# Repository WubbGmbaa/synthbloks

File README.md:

## Project to be renamed. Suggestions appreciated.

# SynthBloks
SynthBloks are modular synthesizer modules in a fun form factor.

### Roadmap
Until the first release of this form factor, the standards described here are subject to change, as issues are fixed and features are added. As part of the process involved in designing and testing the form factor, modules will be designed based on pre-existing, open-source circuits. These modules will also serve a secondary purpose as a "proof of concept" to demonstrate the format, and are hosted in the [synthbloks-PoC repository](https://github.com/WubbGmbaa/synthbloks_POC). Once these "proof of concept" modules have been used to test and change the SynthBloks standard form factor, the first release of the form factor (this repository) will be made. After the first official release of the standards described here, modules will be developed from original circuits, and hosted in their own repositories.

### Development
This repository contains documentation about the standard, as well as resources for desiging modules. Technical details about the form factor can be found [within the documentation](../docs/FormFactor.md).
Proof-of-concept modules were previously also held here, but have since been moved to [their own repository](https://github.com/WubbGmbaa/synthbloks_POC).

### Legal Stuff
First-party modules are licensed under a [Creative Commons Attribution-ShareAlike 4.0 International License](http://creativecommons.org/licenses/by-sa/4.0/).
The form factor itself is licensed under a [Creative Commons Attribution-NonCommercial 4.0 International License](http://creativecommons.org/licenses/by-nc/4.0/).
Third-party modules are the property of their creators.

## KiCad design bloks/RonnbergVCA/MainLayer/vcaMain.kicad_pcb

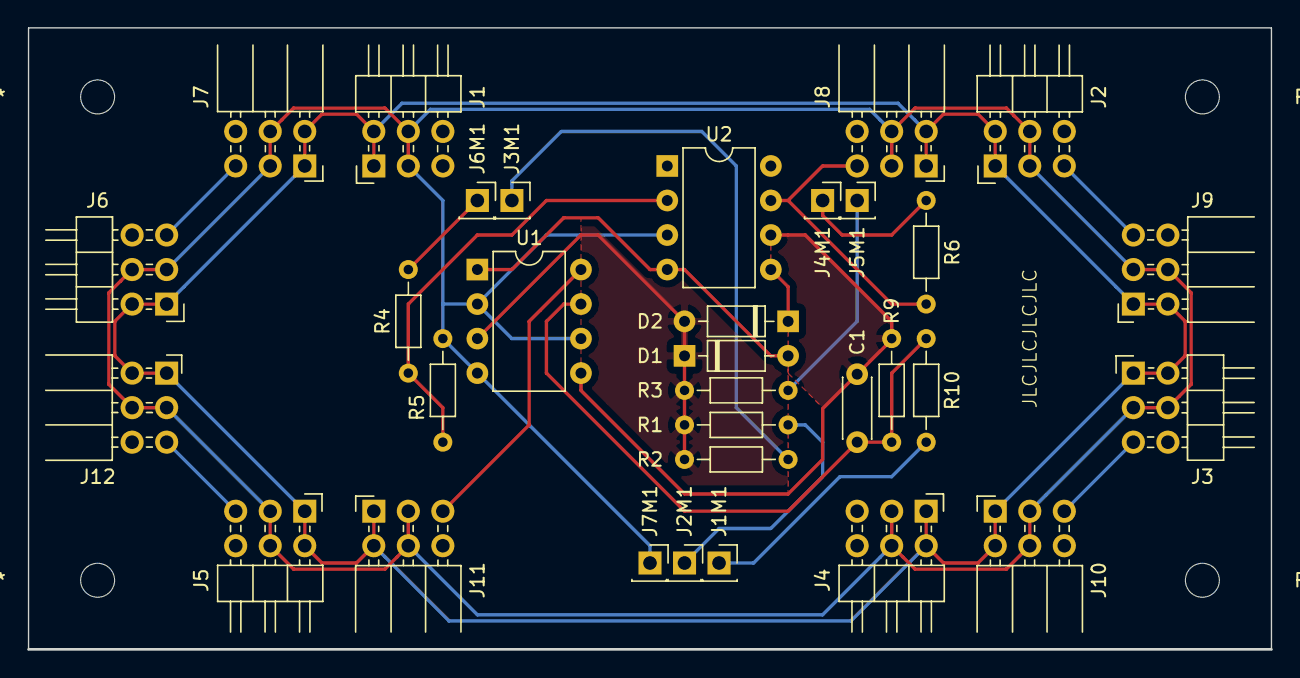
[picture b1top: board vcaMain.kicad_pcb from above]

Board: 2 copper layers, 91.4 x 45.7 mm, 32 parts (0 on the bottom side), 15 nets.

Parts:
C1: 33pF; C_Disc_D4.3mm_W1.9mm_P5.00mm
D1, D2: 1N4148; D_DO-35_SOD27_P7.62mm_Horizontal
J1, J2, J3, J4, J5, J6: Conn_02x03_Odd_Even; PinHeader_2x03_P2.54mm_Horizontal-overedge
J1M1, J2M1, J3M1, J4M1, J5M1, J6M1, J7M1: Conn_01x01; PinSocket_1x01_P2.54mm_Vertical
J7, J8, J9, J10, J11, J12: Conn_02x03_Odd_Even; PinSocket_2x03_P2.54mm_Horizontal-overedge
R1, R2, R3, R4: 100k; R_Axial_DIN0204_L3.6mm_D1.6mm_P7.62mm_Horizontal
R5: 220; R_Axial_DIN0204_L3.6mm_D1.6mm_P7.62mm_Horizontal
R6: 20k; R_Axial_DIN0204_L3.6mm_D1.6mm_P7.62mm_Horizontal
R9: 560k; R_Axial_DIN0204_L3.6mm_D1.6mm_P7.62mm_Horizontal
R10: 1k; R_Axial_DIN0204_L3.6mm_D1.6mm_P7.62mm_Horizontal
U1: TL072; DIP-8_W7.62mm
U2: CA3080; DIP-8_W7.62mm

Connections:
+5V: J1.1, J1.2, J2.1, J2.2, J3.1, J3.2, J4.1, J4.2, J5.1, J5.2, J6.1, J6.2, J7.1, J7.2, J8.1, J8.2, J9.1, J9.2, J10.1, J10.2, J11.1, J11.2, J12.1, J12.2
+12V: J1.5, J1.6, J2.5, J2.6, J3.5, J3.6, J4.5, J4.6, J5.5, J5.6, J6.5, J6.6, J7.5, J7.6, J8.5, J8.6, J9.5, J9.6, J10.5, J10.6, J11.5, J11.6, J12.5, J12.6, R6.2, U1.8, U2.7
GND: J1.3, J1.4, J2.3, J2.4, J3.3, J3.4, J4.3, J4.4, J5.3, J5.4, J6.3, J6.4, J7.3, J7.4, J7M1.1, J8.3, J8.4, J9.3, J9.4, J10.3, J10.4, J11.3, J11.4, J12.3, J12.4, R5.2, U1.2, U1.4, U1.6, U2.3
unnamed: C1.1, R9.1, R10.2, U1.7
unnamed: C1.2, R9.2, U1.5, U2.6
unnamed: D1.1, D2.2, R1.1, R2.1, R3.1, U1.3
unnamed: D1.2, U1.1, U2.4
unnamed: D2.1, U2.5
unnamed: J1M1.1, R10.1
unnamed: J2M1.1, R1.2
unnamed: J3M1.1, R2.2
unnamed: J4M1.1, R6.1
unnamed: J5M1.1, R3.2
unnamed: J6M1.1, R4.2
unnamed: R4.1, R5.1, U2.2

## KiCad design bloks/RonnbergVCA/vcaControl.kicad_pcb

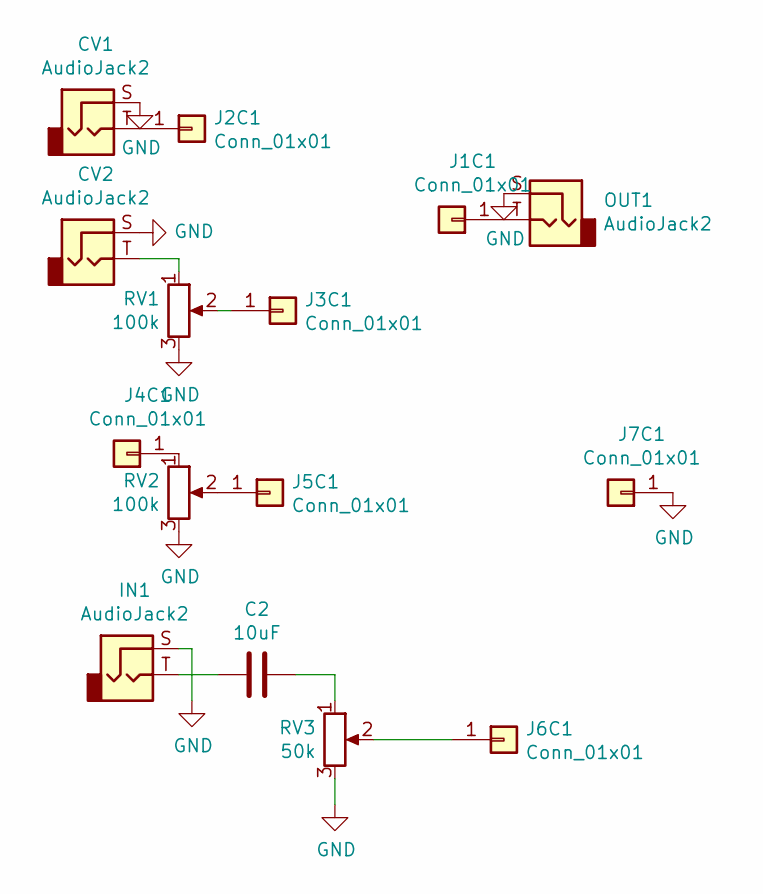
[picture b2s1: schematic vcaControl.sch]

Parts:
C2: 10uF; C_Disc_D4.3mm_W1.9mm_P5.00mm
CV1, CV2: AudioJack2; Jack_3.5mm_QingPu_WQP-PJ398SM_Vertical_CircularHoles
IN1: AudioJack2; Jack_3.5mm_QingPu_WQP-PJ398SM_Vertical_CircularHoles
J1C1, J2C1, J3C1, J4C1, J5C1, J6C1, J7C1: Conn_01x01; PinHeader_1x01_P2.54mm_Vertical
OUT1: AudioJack2; Jack_3.5mm_QingPu_WQP-PJ398SM_Vertical_CircularHoles
RV1, RV2: 100k; RV16A-41-JRL
RV3: 50k; RV16A-41-JRL

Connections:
+5V: CV1.S, CV2.S, IN1.S, J7C1.1, OUT1.S, RV1.3, RV2.3, RV3.3
unnamed: C2.1, RV3.1
unnamed: C2.2, IN1.T
unnamed: CV1.T, J2C1.1
unnamed: CV2.T, RV1.1
unnamed: J1C1.1, OUT1.T
unnamed: J3C1.1, RV1.2
unnamed: J4C1.1, RV2.1
unnamed: J5C1.1, RV2.2
unnamed: J6C1.1, RV3.2

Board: 2 copper layers, 14 parts (0 on the bottom side), 10 nets, no tracks yet.

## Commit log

2019-04-22 Better third party list form
2019-04-29 Split Ronnberg VCA into seperate projects for control and main
2019-05-01 pcb layout
2019-05-01 added 3d model, board alignment fixes
2019-05-01 reorganized VCA project folder hierarchy
2019-05-01 Removed Duplicates
2019-05-02 logo added
2019-05-02 small adjustments, plotted gerbers
2019-05-02 copper pours'
2019-05-02 copper pours
2019-05-02 exported gerbers
2019-05-03 zipped gerbers for production
2019-05-05 Repurposed vco85 as lfo85.
2019-05-05 Added -12v rail to power headers
2019-05-05 Replaced main board Fritzing file with Kicad project. Old file kept for reference/posterity.
2019-05-22 Added breadboard layout for prototype testing
2019-06-19 Added TODO
2019-11-20 Specifications elaborated slightly, CV description adjusted to match planned changes
2019-11-20 Moved PoC and pre-release modules to new repo, named synthbloks_poc. Adjusted readme to reflect this change.
2019-11-20 moved TODO.md to synthbloks_PoC repo
2021-01-12 better description of electrical standards
